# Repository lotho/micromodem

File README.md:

# micromodem
Port of the MicroModem board (https://github.com/markqvist/MicroModem) to Arduino Nano and build it in KiCAD

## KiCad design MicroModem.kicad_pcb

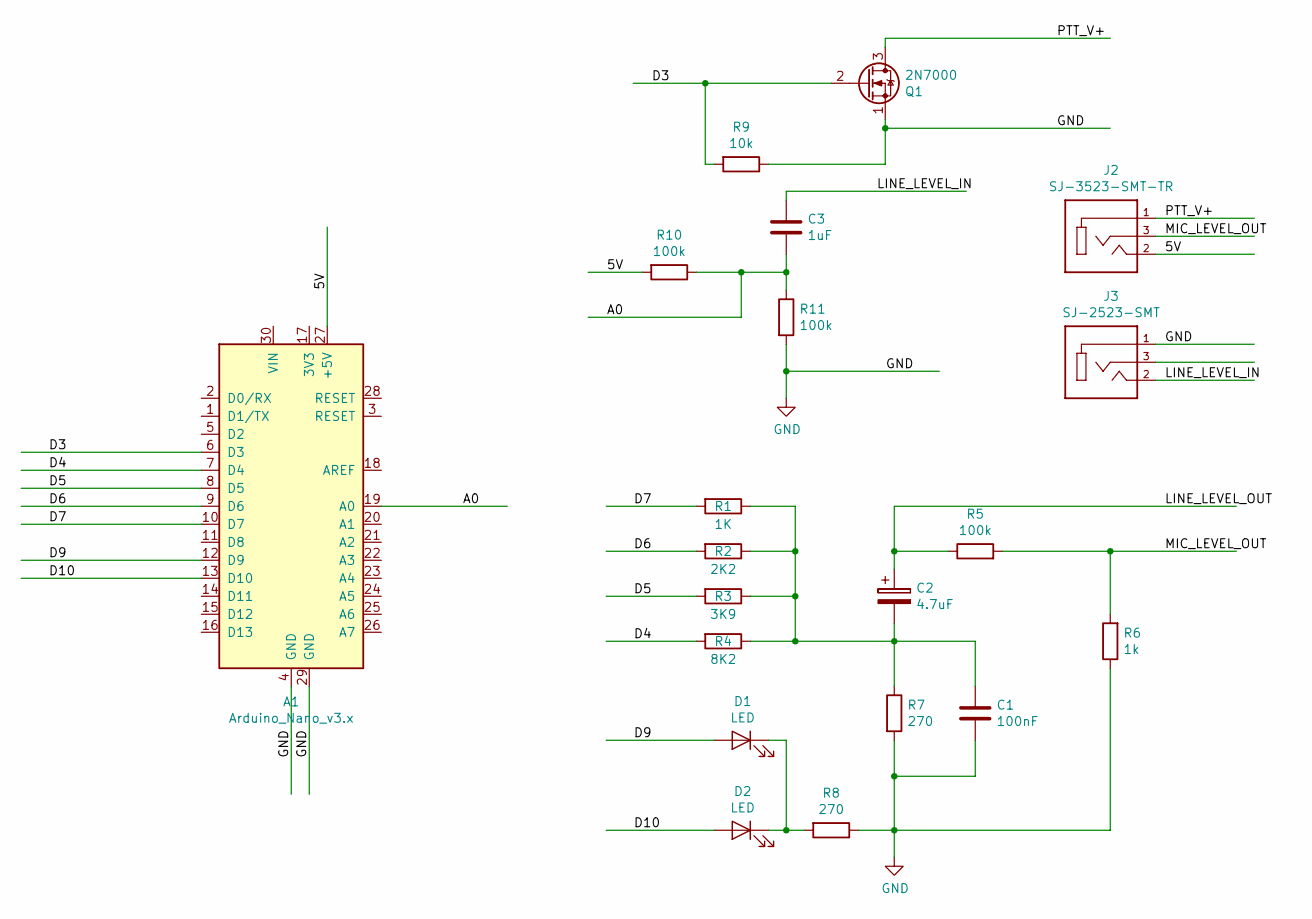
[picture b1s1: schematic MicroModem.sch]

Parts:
A1: Arduino_Nano_v3.x; Arduino_Nano
C1: 100nF; C_1206_3216Metric_Pad1.42x1.75mm_HandSolder
C2: 4.7uF; CP_Elec_4x5.4
C3: 1uF; C_1206_3216Metric_Pad1.42x1.75mm_HandSolder
D1, D2: LED; LED_0805_2012Metric_Pad1.15x1.40mm_HandSolder
J2: SJ-3523-SMT-TR; CUI_SJ-3523-SMT-TR
J3: SJ-2523-SMT; CUI_SJ-2523-SMT
Q1: 2N7000; TO-92L_HandSolder
R1: 1K; R_0805_2012Metric_Pad1.15x1.40mm_HandSolder
R2: 2K2; R_0805_2012Metric_Pad1.15x1.40mm_HandSolder
R3: 3K9; R_0805_2012Metric_Pad1.15x1.40mm_HandSolder
R4: 8K2; R_0805_2012Metric_Pad1.15x1.40mm_HandSolder
R5, R10, R11: 100k; R_0805_2012Metric_Pad1.15x1.40mm_HandSolder
R6: 1k; R_0805_2012Metric_Pad1.15x1.40mm_HandSolder
R7, R8: 270; R_0805_2012Metric_Pad1.15x1.40mm_HandSolder
R9: 10k; R_0805_2012Metric_Pad1.15x1.40mm_HandSolder

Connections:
/5V: A1.27 (+5V), J2.2, R10.2
/A0: A1.19 (A0), C3.2, R10.1, R11.1
/D3: A1.6 (D3), Q1.2 (G), R9.2
/D4: A1.7 (D4), R4.2
/D5: A1.8 (D5), R3.2
/D6: A1.9 (D6), R2.2
/D7: A1.10 (D7), R1.2
/D9: A1.12 (D9), D1.2 (A)
/D10: A1.13 (D10), D2.2 (A)
/LINE_LEVEL_IN: C3.1, J3.2
/LINE_LEVEL_OUT: C2.1, R5.1
/MIC_LEVEL_OUT: J2.3, R5.2, R6.2
/PTT_V+: J2.1, Q1.3 (D)
GND: A1.4 (GND), A1.29 (GND), C1.2, J3.1, Q1.1 (S), R6.1, R7.2, R8.1, R9.1, R11.2
unnamed: C1.1, C2.2, R1.1, R2.1, R3.1, R4.1, R7.1
unnamed: D1.1 (K), D2.1 (K), R8.2

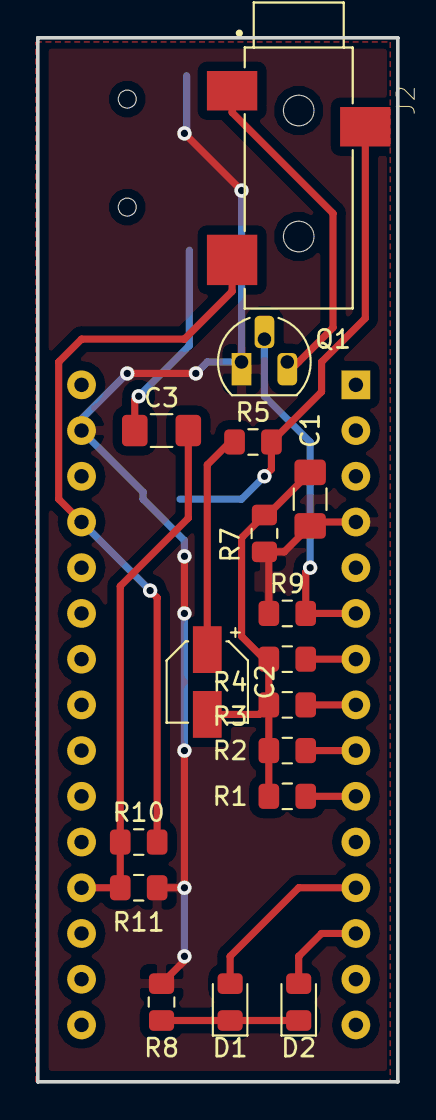
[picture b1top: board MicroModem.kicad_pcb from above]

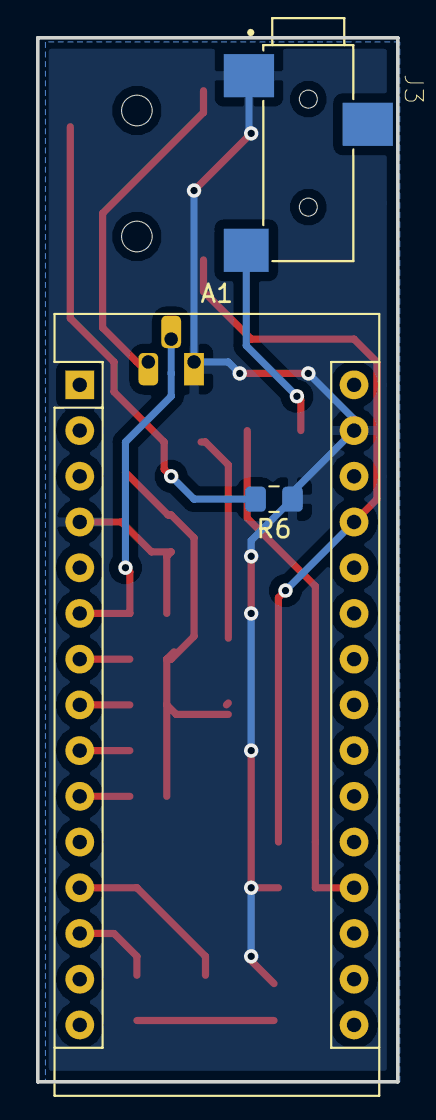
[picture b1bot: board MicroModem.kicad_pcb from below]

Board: 2 copper layers, 20.0 x 58.0 mm, 20 parts (3 on the bottom side), 16 nets.

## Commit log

2019-01-10 kicad files created
2019-01-13 redudant files removed
